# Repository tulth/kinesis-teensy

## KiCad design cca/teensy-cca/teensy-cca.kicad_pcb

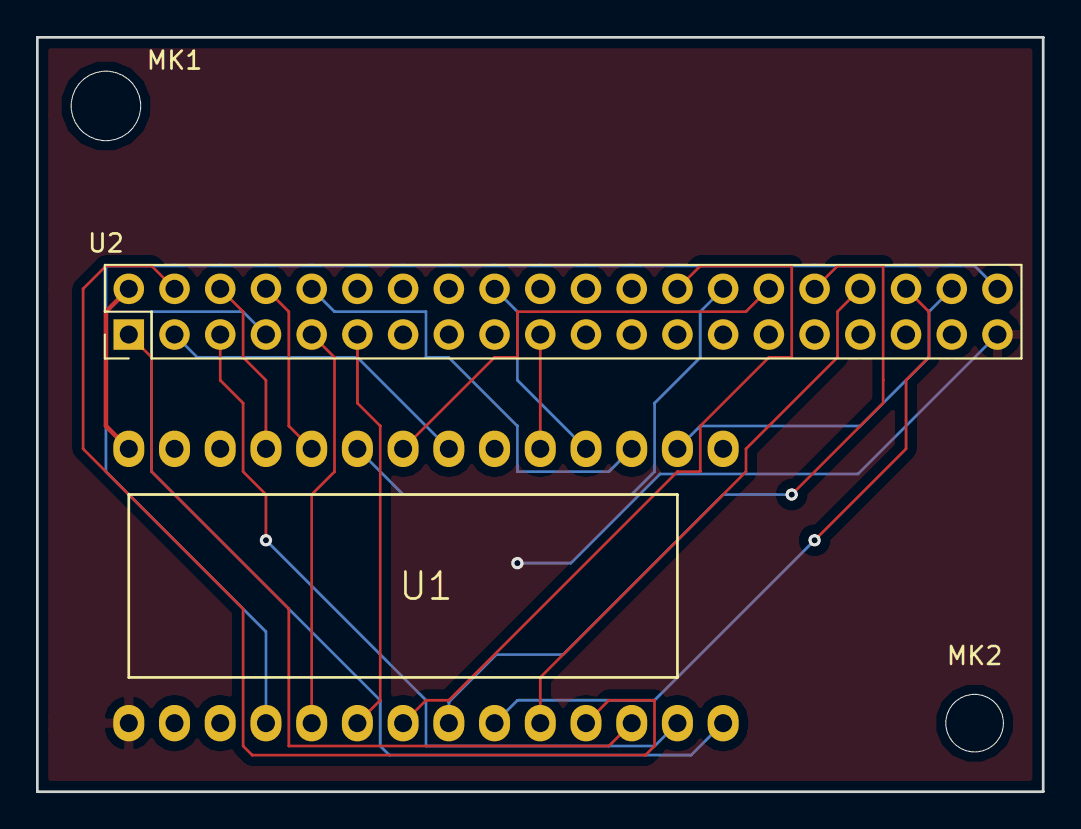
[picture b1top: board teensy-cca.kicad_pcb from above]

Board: 2 copper layers, 55.9 x 41.9 mm, 4 parts (0 on the bottom side), 22 nets.

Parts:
MK1, MK2: Mounting_Hole; MountingHole_3.2mm_M3_ISO14580
U1: TEENSY-3.2; Teensy-3.2
U2: at89s8253-40p6; Pin_Header_Straight_2x20_Pitch2.54mm

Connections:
+5V: U1.26, U2.40
/kbd_buzzer: U1.16, U2.32
/kbd_caps_led: U1.12, U2.4
/kbd_keypad_btn: U1.3, U2.5
/kbd_keypad_led: U1.11, U2.3
/kbd_matrix1: U1.2, U2.21
/kbd_matrix2: U1.14, U2.22
/kbd_matrix3: U1.7, U2.23
/kbd_matrix4: U1.8, U2.24
/kbd_matrix5: U1.6, U2.25
/kbd_matrix6: U1.20, U2.26
/kbd_matrix7: U1.21, U2.27
/kbd_matrix8: U1.5, U2.28
/kbd_num_led: U1.10, U2.1
/kbd_p138_a: U1.9, U2.39
/kbd_p138_b: U1.23, U2.38
/kbd_p138_c: U1.22, U2.37
/kbd_p138_nen: U1.17, U2.10
/kbd_p138_sel: U1.15, U2.36
/kbd_program_btn: U1.4, U2.6
/kbd_scroll_led: U1.19, U2.2
GND: U1.27, U2.20

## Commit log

2018-02-02 initial gitignore and grab my kicad common submodule
2018-02-02 make cca folder, will probably have firmware too
2018-02-03 add tmk submodule
2018-02-03 initial teensy wire mapping schematic
2018-02-03 make firmware folder and move c code there
2018-02-03 move scroll lock off teensy led pin
2018-02-03 use kicad_common that includes kinesis uc
2018-02-03 blinky led test firmware
2018-02-10 commit cca files for first release to osh park
